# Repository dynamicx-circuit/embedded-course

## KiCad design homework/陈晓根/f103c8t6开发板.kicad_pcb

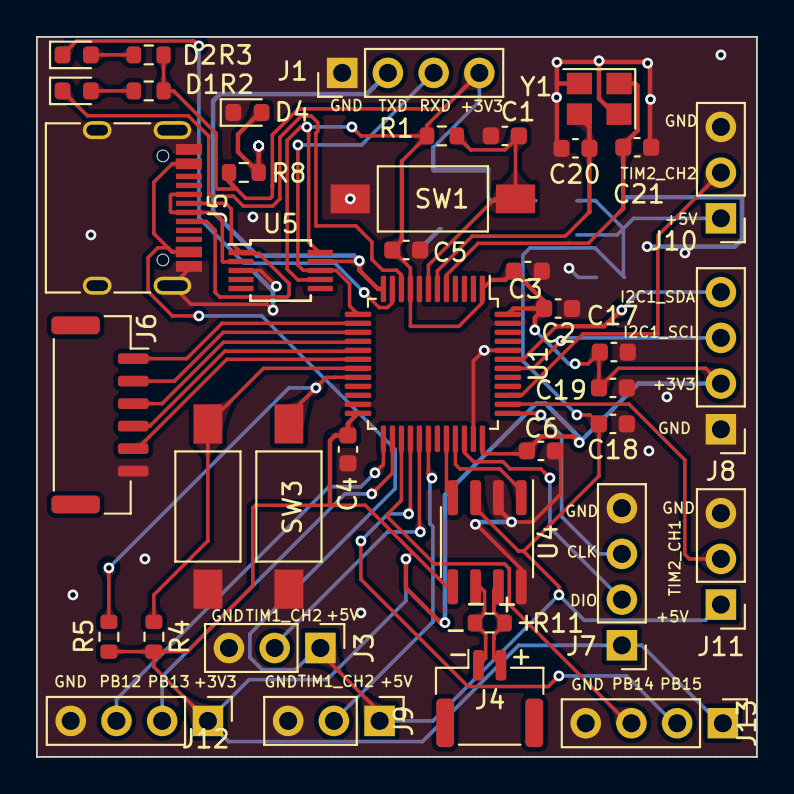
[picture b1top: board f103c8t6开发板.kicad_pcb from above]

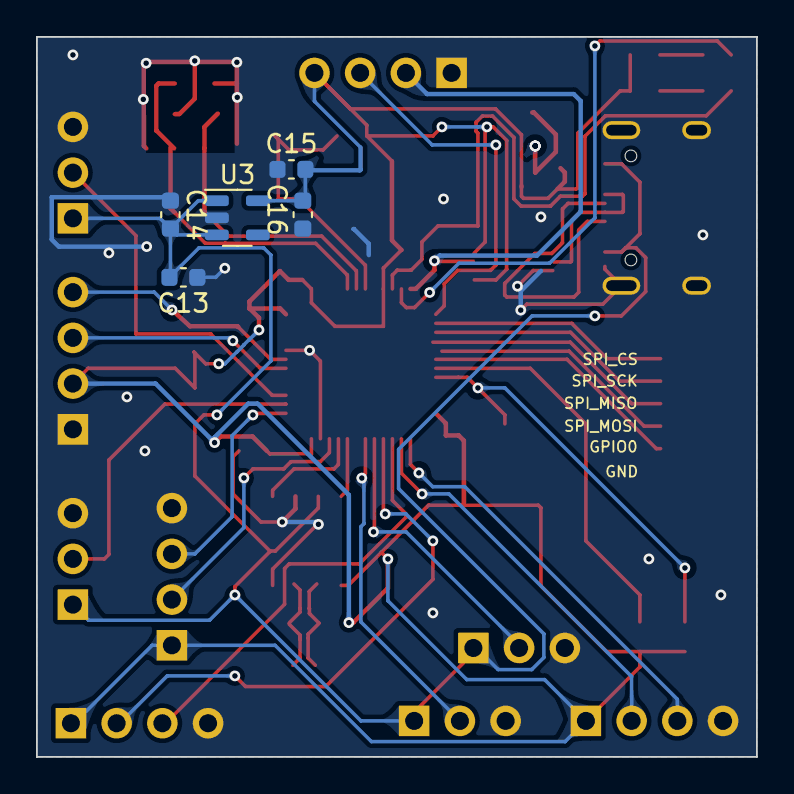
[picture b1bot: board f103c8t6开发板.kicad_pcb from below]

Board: 2 copper layers, 40.0 x 40.0 mm, 45 parts (5 on the bottom side), 38 nets.

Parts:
C1, C2, C3, C4, C5, C6, C14, C15, C17, C18, C19: 100n; C_0603_1608Metric
C13, C16: 2.2u; C_0603_1608Metric
C20, C21: 12p; C_0603_1608Metric
D1, D2: LED; LED_0603_1608Metric
D4: RED; LED_0603_1608Metric
J1, J7, J8, J12, J13: Conn_01x04; PinHeader_1x04_P2.54mm_Vertical
J3, J9, J10, J11: Conn_01x03; PinHeader_1x03_P2.54mm_Vertical
J4: Conn_01x02; JST_GH_SM02B-GHS-TB_1x02-1MP_P1.25mm_Horizontal
J5: USB_C_Receptacle_USB2.0; USB_C_Receptacle_HRO_TYPE-C-31-M-12
J6: Conn_01x06; JST_GH_SM06B-GHS-TB_1x06-1MP_P1.25mm_Horizontal
R1, R4, R5, R8: 10k; R_0603_1608Metric
R2, R3: 1K; R_0603_1608Metric
R11: 120; R_0603_1608Metric
SW1, SW2, SW3: SW; SW_SPST_FSMSM
U1: STM32F103C8Tx; LQFP-48_7x7mm_P0.5mm
U3: HX9193-33GB; SOT-23-5
U4: TJA1051T-3; SOIC-8_3.9x4.9mm_P1.27mm
U5: CH340E; MSOP-10_3x3mm_P0.5mm
Y1: 12M; Crystal_SMD_3225-4Pin_3.2x2.5mm

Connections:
+3V3: C2.2, C3.2, C4.2, C5.2, C6.2, C15.2, C16.2, C17.2, C19.1, J1.4, J7.1, J8.2, J12.1, J13.1, R1.2, R2.1, R3.1, R4.2, R5.2, R8.2, U1.1 (Vbat), U1.9 (Vin_A), U1.24 (Vin), U1.36 (Vin), U1.48 (Vin), U3.5 (Vout), U4.5 (VIO), U5.7 (VCC), U5.10 (V3)
+5V: C13.2, C14.2, C18.2, J3.1, J5.A4 (VBUS), J5.A9 (VBUS), J5.B4 (VBUS), J5.B9 (VBUS), J9.1, J10.1, J11.1, U3.1 (Vin), U3.3 (EN), U4.3 (VCC)
/Connector/+: J4.2, R11.2, U4.7 (CANH)
/Connector/-: J4.1, R11.1, U4.6 (CANL)
/Connector/CAN_RX: U1.32 (PA11), U4.4 (RXD)
/Connector/CAN_TX: U1.33 (PA12), U4.1 (TXD)
/Connector/DN: J5.A7 (D-), J5.B7 (D-), U5.2 (UD-)
/Connector/DP: J5.A6 (D+), J5.B6 (D+), U5.1 (UD+)
/Connector/GPIO0: J6.5, U1.18 (PB0)
/Connector/I2C1_SCL: J8.3, U1.42 (PB6)
/Connector/I2C1_SDA: J8.4, U1.43 (PB7)
/Connector/PB12: J12.3, U1.25 (PB12)
/Connector/PB13: J12.2, U1.26 (PB13)
/Connector/PB14: J13.3, U1.27 (PB14)
/Connector/PB15: J13.2, U1.28 (PB15)
/Connector/RXD: J1.3, U1.13 (PA3), U5.8 (TXD)
/Connector/SPI_CS: J6.1, U1.14 (PA4)
/Connector/SPI_MISO: J6.3, U1.16 (PA6)
/Connector/SPI_MOSI: J6.4, U1.17 (PA7)
/Connector/SPI_SCK: J6.2, U1.15 (PA5)
/Connector/TIM1_CH: J3.2, U1.29 (PA8)
/Connector/TIM1_CH2: J9.2, U1.30 (PA9)
/Connector/TIM2_CH1: J11.2, U1.38 (PA15)
/Connector/TIM2_CH2: J10.2, U1.39 (PB3)
/Connector/TXD: J1.2, U1.12 (PA2), U5.9 (RXD)
/MCU/CLK: J7.3, U1.37 (PA14)
/MCU/DIO: J7.2, U1.34 (PA13)
/MCU/KEY1: R4.1, SW2.1, U1.19 (PB1)
/MCU/KEY2: R5.1, SW3.1, U1.20 (PB2)
/MCU/LED1: D1.1 (K), U1.10 (PA0)
/MCU/LED2: D2.1 (K), U1.11 (PA1)
/MCU/RESET: C1.2, R1.1, SW1.1, U1.7 (~RST)
/MCU/XTAL_I: C21.1, U1.5 (PD0), Y1.1
/MCU/XTAL_O: C20.2, U1.6 (PD1), Y1.3
GND: C1.1, C2.1, C3.1, C4.1, C5.1, C6.1, C13.1, C14.1, C15.1, C16.1, C17.1, C18.1, C19.2, C20.1, C21.2, D4.1 (K), J1.1, J3.3, J5.A1 (GND), J5.A12 (GND), J5.B1 (GND), J5.B12 (GND), J5.S1 (SHIELD), J6.6, J7.4, J8.1, J9.3, J10.3, J11.3, J12.4, J13.4, SW1.2, SW2.2, SW3.2, U1.8 (GND_A), U1.23 (GND), U1.35 (GND), U1.44 (BOOT0), U1.47 (GND), U3.2 (GND), U4.2 (GND), U4.8 (S), U5.3 (GND), Y1.2, Y1.4
unnamed: D1.2 (A), R2.2
unnamed: D2.2 (A), R3.2
unnamed: D4.2 (A), R8.1

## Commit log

2023-04-13 the first commit of stm32f103c8t6-circuit
2023-04-14 Modify PCH and SCH
2023-04-14 Fix some SCH bugs
2023-04-15 Found the file of homework
2023-04-17 袁汉阔提交了作业
2023-04-19 Lin Yuchuan's commit
2023-04-20 容键超2
2023-04-20 fix some mistakes
2023-04-24 try to resolve conflicts of lyc and main
2023-04-24 Fix some error of 晓根的pcb
2023-04-24 homework
2023-04-24 add silkscream
2023-04-26 最终版本“
    git commit -m最终版本”
